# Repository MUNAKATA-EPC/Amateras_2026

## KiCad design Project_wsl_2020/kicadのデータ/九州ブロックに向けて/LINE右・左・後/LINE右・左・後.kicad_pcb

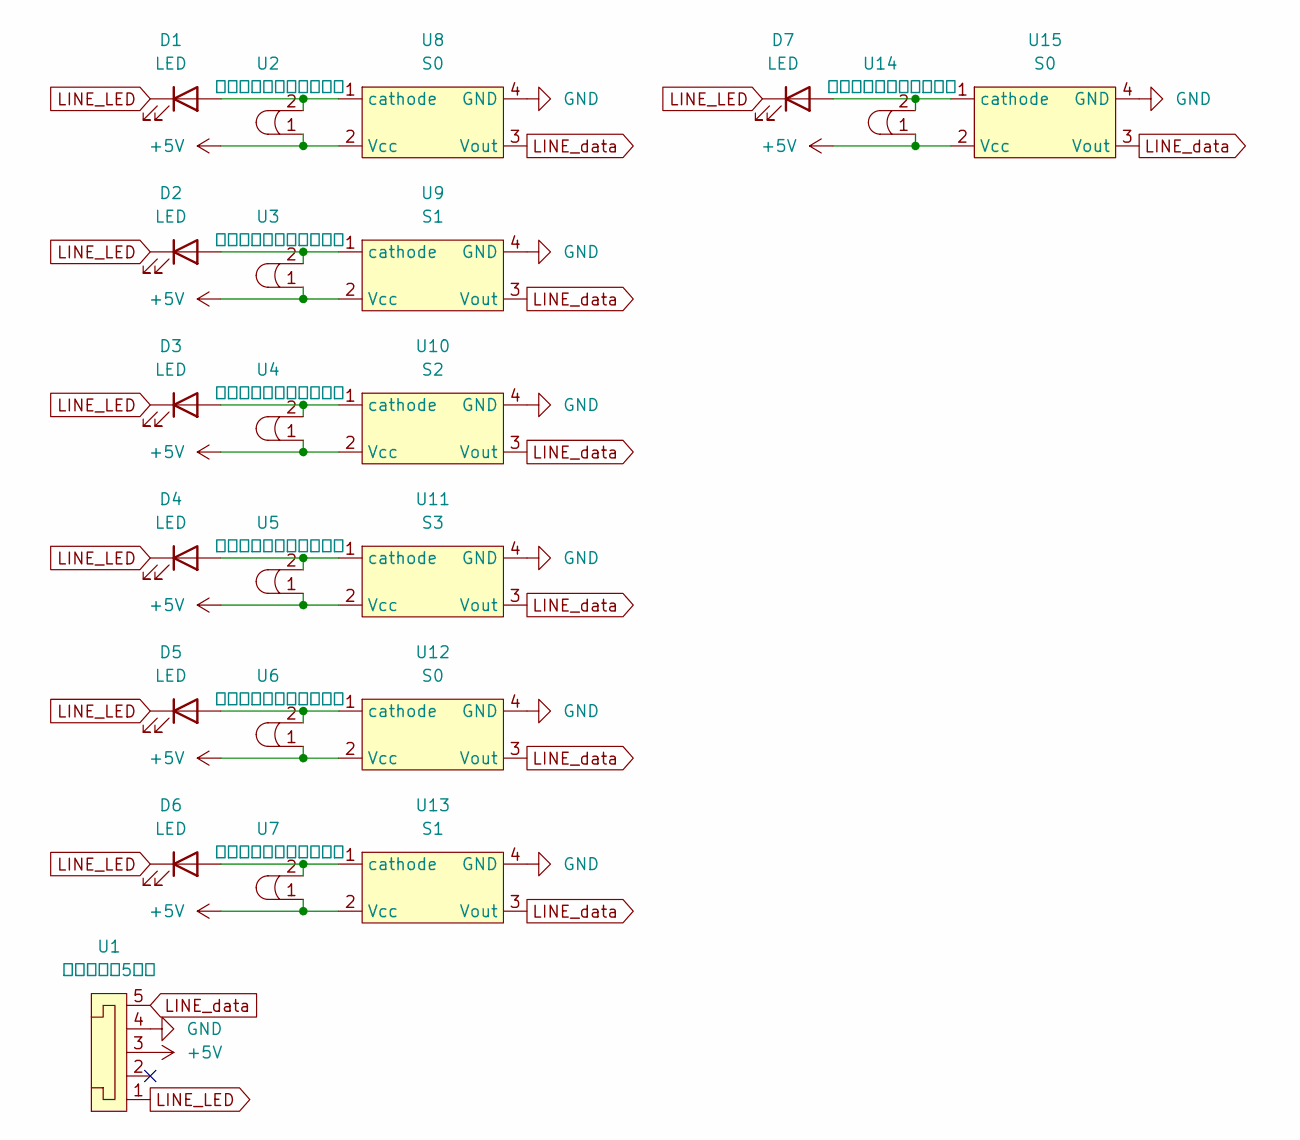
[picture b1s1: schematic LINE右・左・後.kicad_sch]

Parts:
D1, D2, D3, D4, D5, D6, D7: LED
U1: コネクター5ピン; L字コネクター5ピン
U2, U3, U4, U5, U6, U7, U14: セラミックコンデンサー
U8, U12, U15: S0; S4282-51,S7136
U9, U13: S1; S4282-51,S7136
U10: S2; S4282-51,S7136
U11: S3; S4282-51,S7136

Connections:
+5V: U1.3, U2.1, U3.1, U4.1, U5.1, U6.1, U7.1, U8.2 (Vcc), U9.2 (Vcc), U10.2 (Vcc), U11.2 (Vcc), U12.2 (Vcc), U13.2 (Vcc), U14.1, U15.2 (Vcc)
GND: U1.4, U8.4 (GND), U9.4 (GND), U10.4 (GND), U11.4 (GND), U12.4 (GND), U13.4 (GND), U15.4 (GND)
LINE_LED: D1.1 (K), D2.1 (K), D3.1 (K), D4.1 (K), D5.1 (K), D6.1 (K), D7.1 (K), U1.1
LINE_data: U1.5, U8.3 (Vout), U9.3 (Vout), U10.3 (Vout), U11.3 (Vout), U12.3 (Vout), U13.3 (Vout), U15.3 (Vout)
unnamed: D1.2 (A), U2.2, U8.1 (cathode)
unnamed: D2.2 (A), U3.2, U9.1 (cathode)
unnamed: D3.2 (A), U4.2, U10.1 (cathode)
unnamed: D4.2 (A), U5.2, U11.1 (cathode)
unnamed: D5.2 (A), U6.2, U12.1 (cathode)
unnamed: D6.2 (A), U7.2, U13.1 (cathode)
unnamed: D7.2 (A), U14.2, U15.1 (cathode)

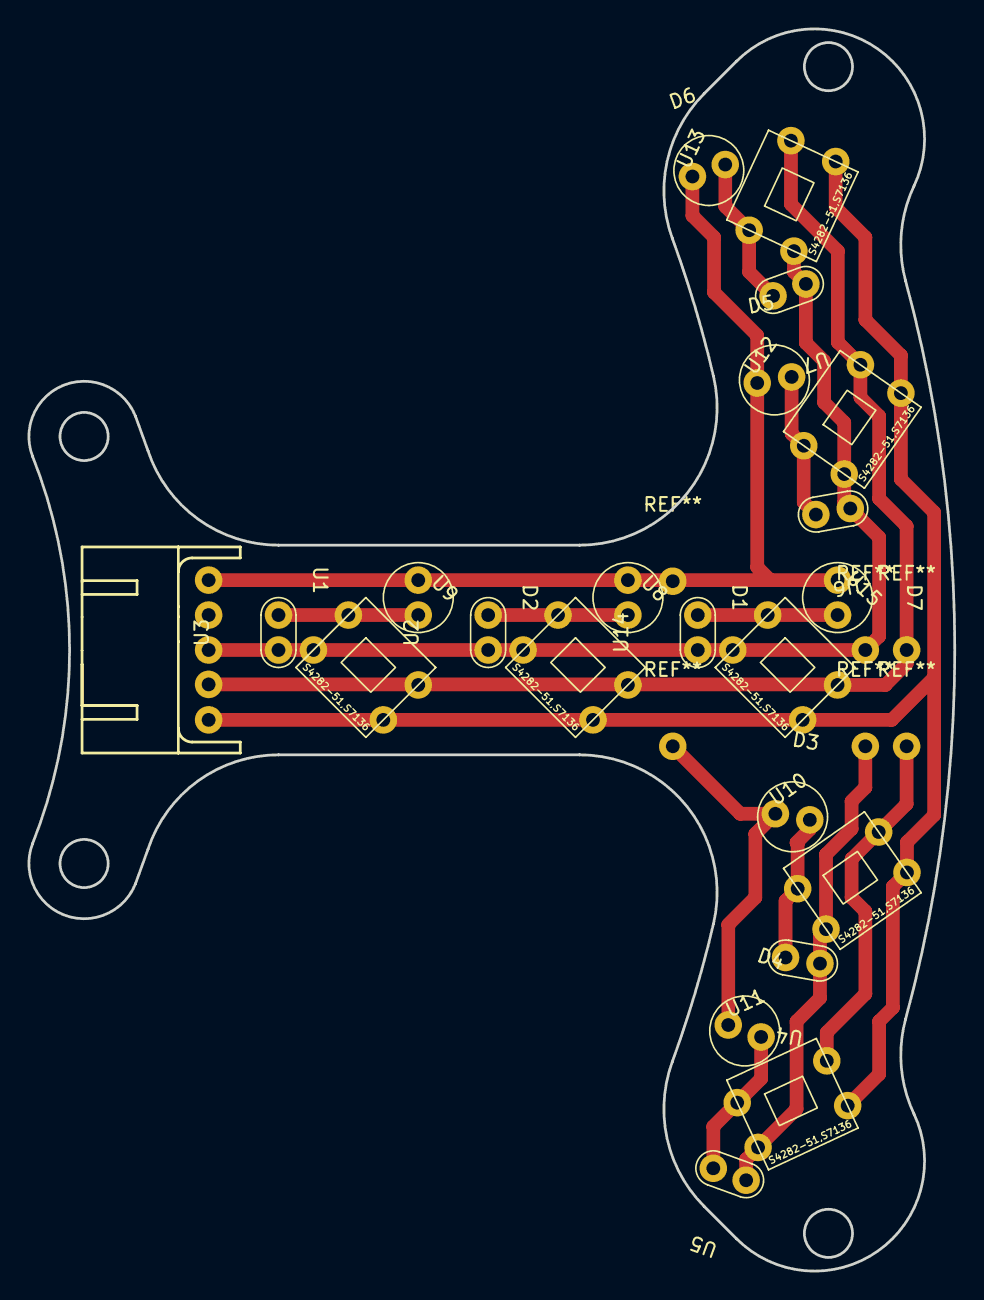
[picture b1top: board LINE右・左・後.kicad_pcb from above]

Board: 2 copper layers, 67.3 x 90.3 mm, 22 parts (0 on the bottom side), 11 nets.

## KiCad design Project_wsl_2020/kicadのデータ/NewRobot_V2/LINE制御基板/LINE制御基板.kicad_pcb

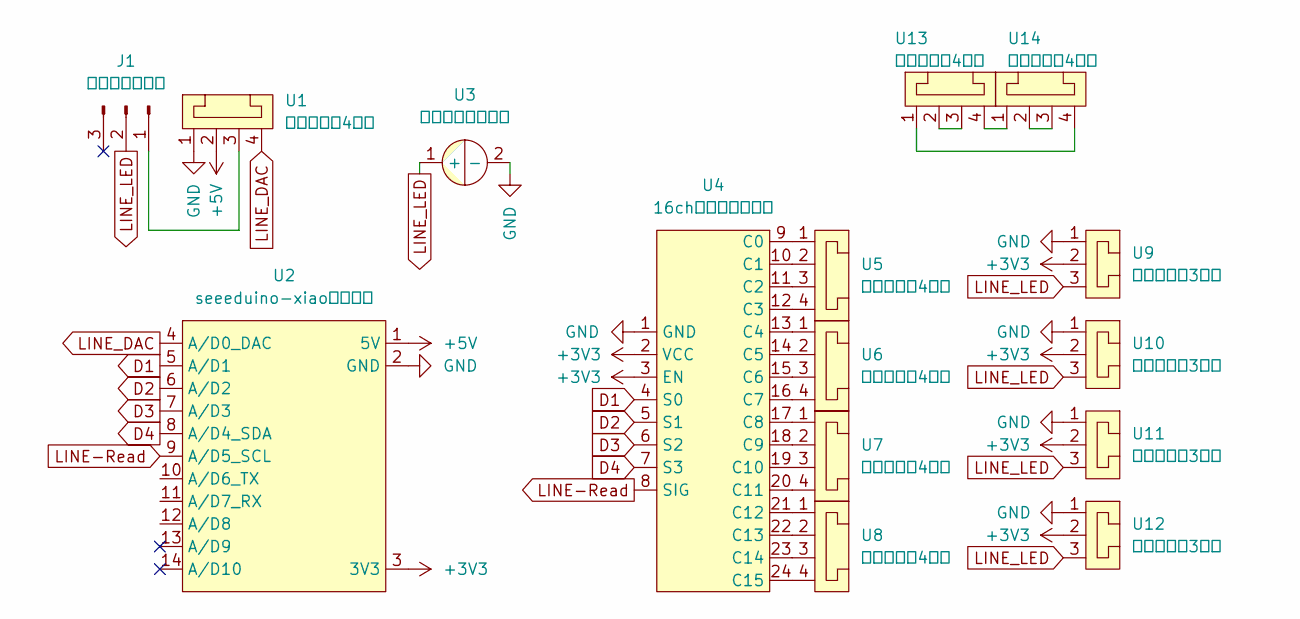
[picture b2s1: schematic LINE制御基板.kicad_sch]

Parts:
J1: トグルスイッチ; 基板用トグルスイッチ
U1, U5, U6, U7, U8, U13, U14: コネクター4ピン
U2: seeeduino-xiaoマイコン
U3: 電解コンデンサー
U4: 16chマルチプレクサ; マルチプレクサ
U9, U10, U11, U12: コネクター3ピン

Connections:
+3V3: U2.3 (3V3), U4.2 (VCC), U9.2, U10.2, U11.2, U12.2
+5V: U1.2, U2.1 (5V)
D1: U2.5 (A/D1), U4.4 (S0)
D2: U2.6 (A/D2), U4.5 (S1)
D3: U2.7 (A/D3), U4.6 (S2)
D4: U2.8 (A/D4_SDA), U4.7 (S3)
GND: U1.1, U2.2 (GND), U3.2 (-), U4.1 (GND), U9.1, U10.1, U11.1, U12.1
LINE_DAC: U1.4, U2.4 (A/D0_DAC)
LINE_LED: J1.2, U3.1 (+), U9.3, U10.3, U11.3, U12.3
unnamed: J1.1, U1.3
unnamed: U4.9 (C0), U5.1
unnamed: U4.10 (C1), U5.2
unnamed: U4.11 (C2), U5.3
unnamed: U4.12 (C3), U5.4
unnamed: U4.13 (C4), U6.1
unnamed: U4.14 (C5), U6.2
unnamed: U4.15 (C6), U6.3
unnamed: U4.16 (C7), U6.4
unnamed: U4.17 (C8), U7.1
unnamed: U4.18 (C9), U7.2
unnamed: U4.19 (C10), U7.3
unnamed: U4.20 (C11), U7.4
unnamed: U4.21 (C12), U8.1
unnamed: U4.22 (C13), U8.2
unnamed: U4.23 (C14), U8.3
unnamed: U4.24 (C15), U8.4
unnamed: U13.1, U14.4
unnamed: U13.2, U13.3
unnamed: U13.4, U14.1
unnamed: U14.2, U14.3

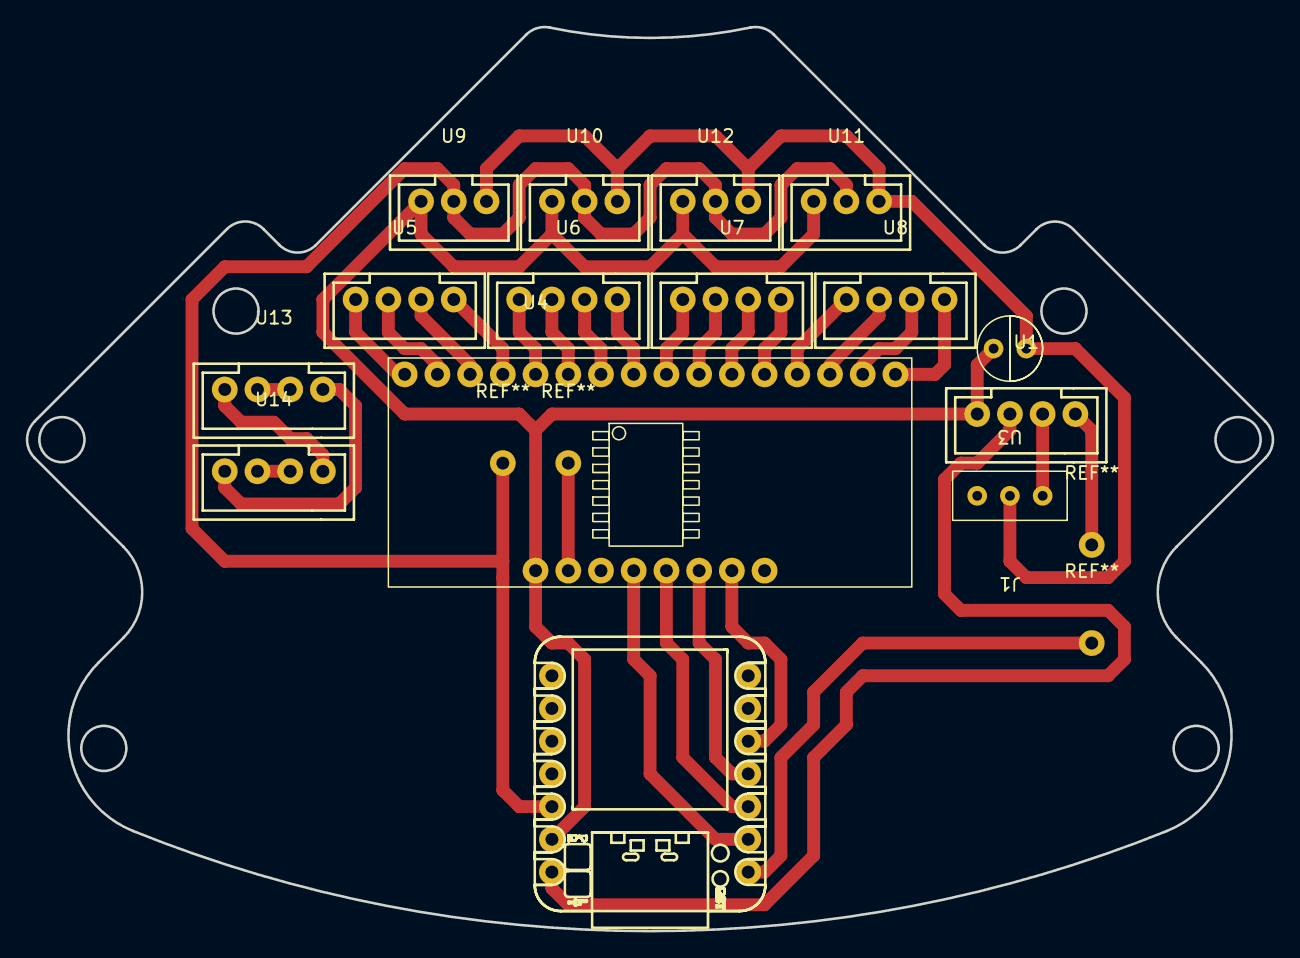
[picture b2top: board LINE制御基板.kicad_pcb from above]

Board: 2 copper layers, 96.7 x 70.2 mm, 15 parts (0 on the bottom side), 30 nets.

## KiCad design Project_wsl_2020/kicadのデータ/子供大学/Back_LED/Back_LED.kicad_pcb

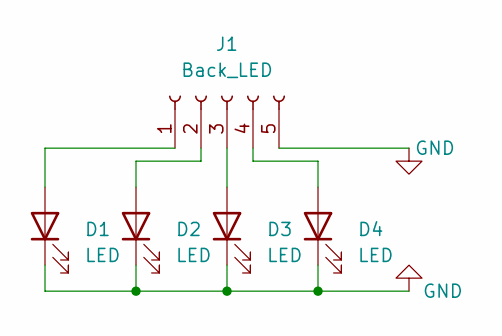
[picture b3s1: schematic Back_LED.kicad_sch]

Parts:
D1, D2, D3, D4: LED; PinSocket_1x02_P2.54mm_Horizontal
J1: Back_LED; PinSocket_1x05_P2.54mm_Vertical

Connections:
GND: D1.1 (K), D2.1 (K), D3.1 (K), D4.1 (K), J1.5
unnamed: D1.2 (A), J1.1
unnamed: D2.2 (A), J1.2
unnamed: D3.2 (A), J1.3
unnamed: D4.2 (A), J1.4

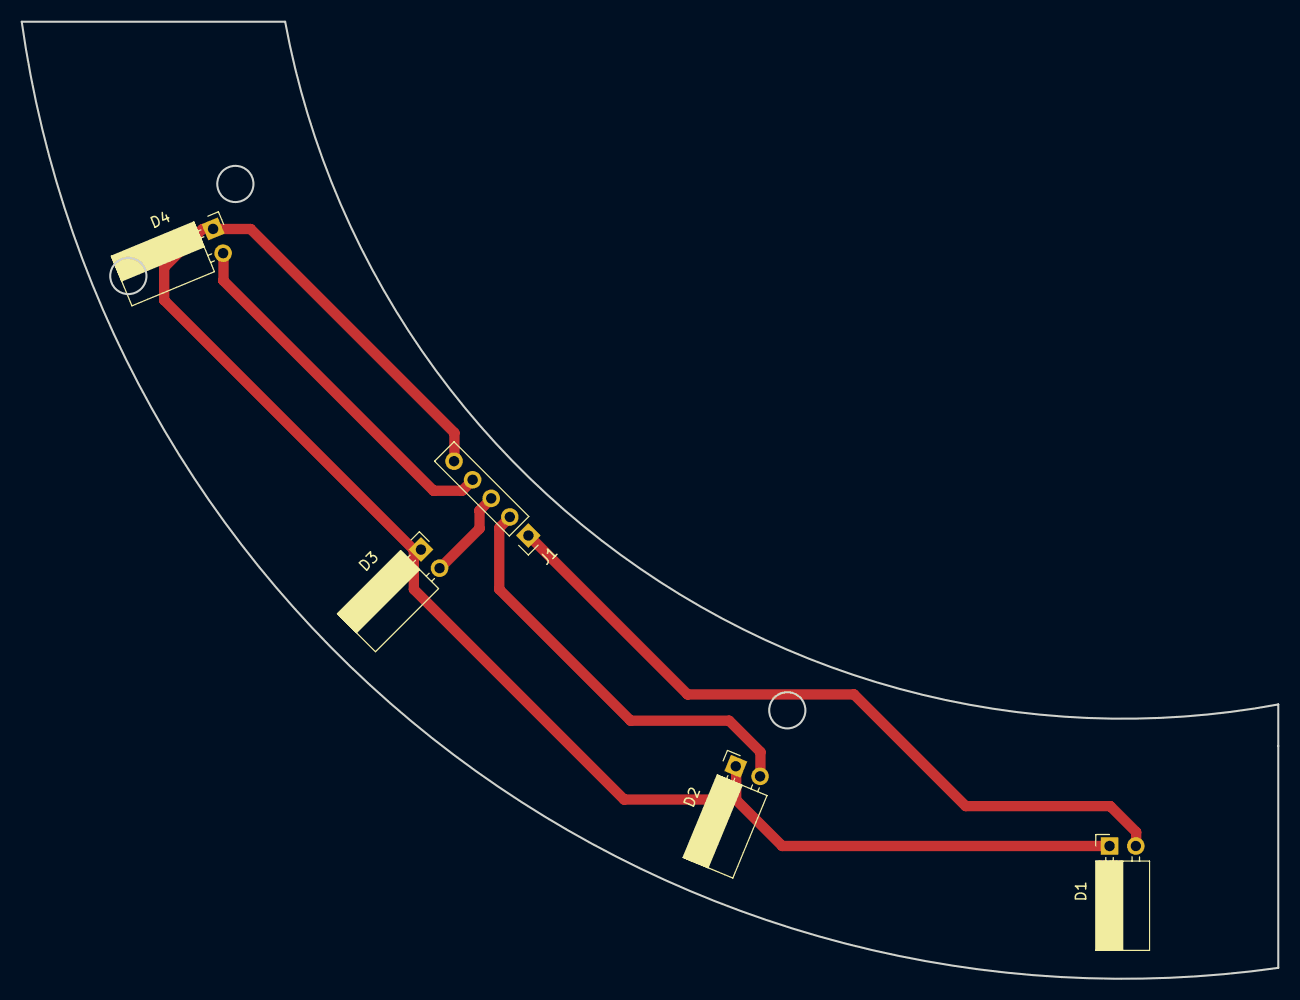
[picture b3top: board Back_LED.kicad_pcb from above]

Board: 2 copper layers, 121.4 x 92.5 mm, 5 parts (0 on the bottom side), 5 nets.

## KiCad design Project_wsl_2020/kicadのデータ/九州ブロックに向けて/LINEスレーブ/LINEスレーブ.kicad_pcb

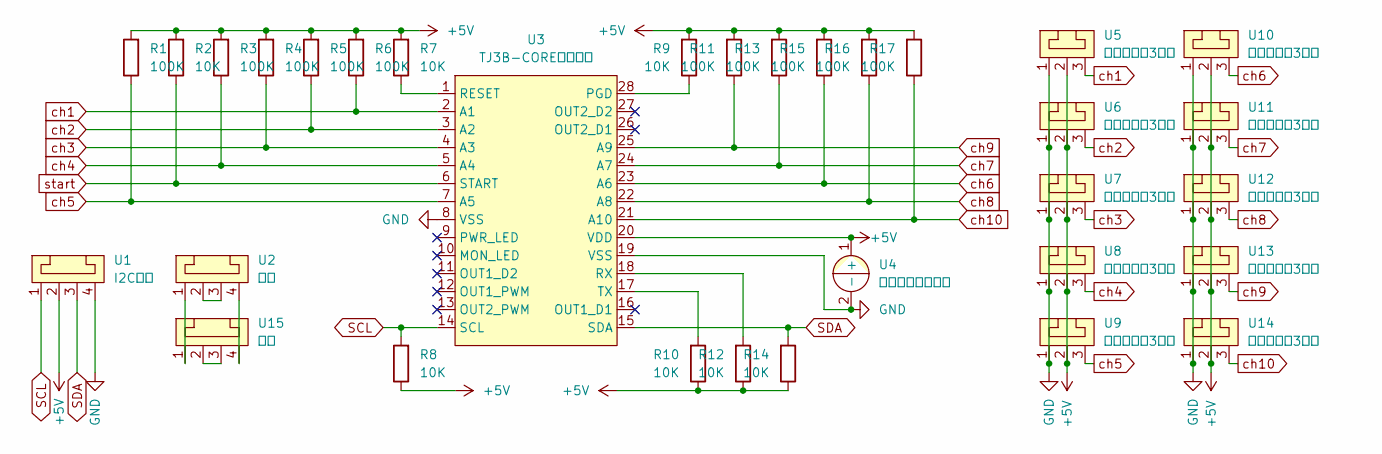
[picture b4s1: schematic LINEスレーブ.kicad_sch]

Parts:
R1, R3, R4, R5, R6, R11, R13, R15, R16, R17: 100K; 抵抗
R2, R7, R8, R9, R10, R12, R14: 10K; 抵抗
U1: I2Cピン; コネクター4ピン
U2, U15: 電池; コネクター4ピン
U3: TJ3B-COREマイコン
U4: 電解コンデンサー
U5, U6, U7, U8, U9, U10, U11, U12, U13, U14: コネクター3ピン

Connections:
+5V: R1.2, R2.2, R3.2, R4.2, R5.2, R6.2, R7.2, R8.1, R9.2, R10.1, R11.2, R12.1, R13.2, R14.1, R15.2, R16.2, R17.2, U1.2, U3.20 (VDD), U4.1 (+), U5.2, U6.2, U7.2, U8.2, U9.2, U10.2, U11.2, U12.2, U13.2, U14.2
GND: U1.4, U3.8 (VSS), U3.19 (VSS), U4.2 (-), U5.1, U6.1, U7.1, U8.1, U9.1, U10.1, U11.1, U12.1, U13.1, U14.1
unnamed: R7.1, U3.1 (RESET)
unnamed: R9.1, U3.28 (PGD)
unnamed: R10.2, U3.17 (TX)
unnamed: R12.2, U3.18 (RX)
unnamed: U2.2, U2.3
unnamed: U2.1, U15.1
unnamed: U15.2, U15.3
unnamed: U2.4, U15.4
SCL: R8.2, U1.1, U3.14 (SCL)
SDA: R14.2, U1.3, U3.15 (SDA)
ch1: R6.1, U3.2 (A1), U5.3
ch2: R5.1, U3.3 (A2), U6.3
ch3: R4.1, U3.4 (A3), U7.3
ch4: R3.1, U3.5 (A4), U8.3
ch5: R1.1, U3.7 (A5), U9.3
ch6: R15.1, U3.23 (A6), U10.3
ch7: R13.1, U3.24 (A7), U11.3
ch8: R16.1, U3.22 (A8), U12.3
ch9: R11.1, U3.25 (A9), U13.3
ch10: R17.1, U3.21 (A10), U14.3
start: R2.1, U3.6 (START)

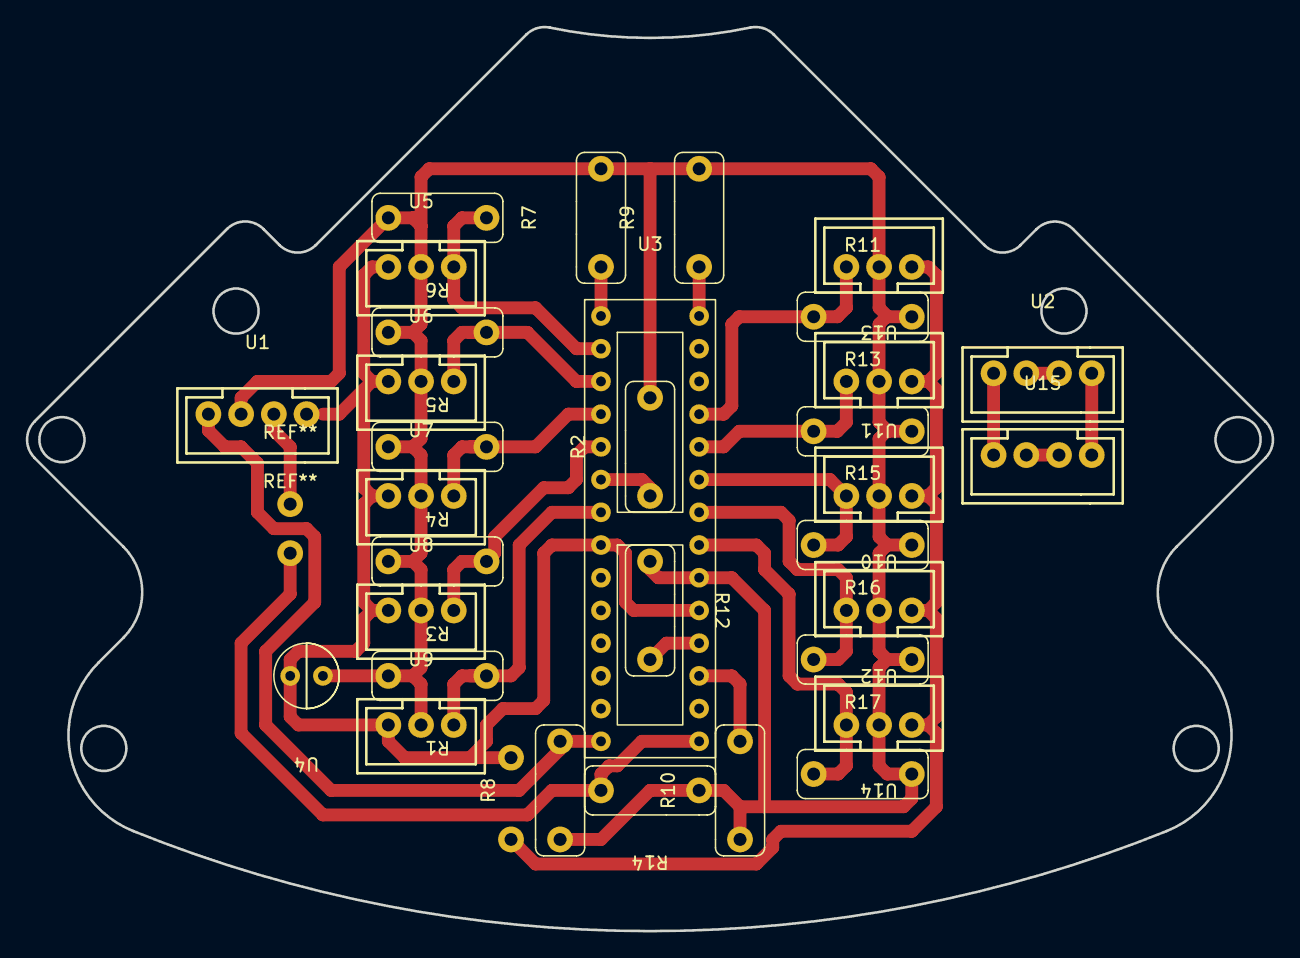
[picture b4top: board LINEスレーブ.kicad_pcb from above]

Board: 2 copper layers, 96.7 x 70.2 mm, 32 parts (0 on the bottom side), 23 nets.

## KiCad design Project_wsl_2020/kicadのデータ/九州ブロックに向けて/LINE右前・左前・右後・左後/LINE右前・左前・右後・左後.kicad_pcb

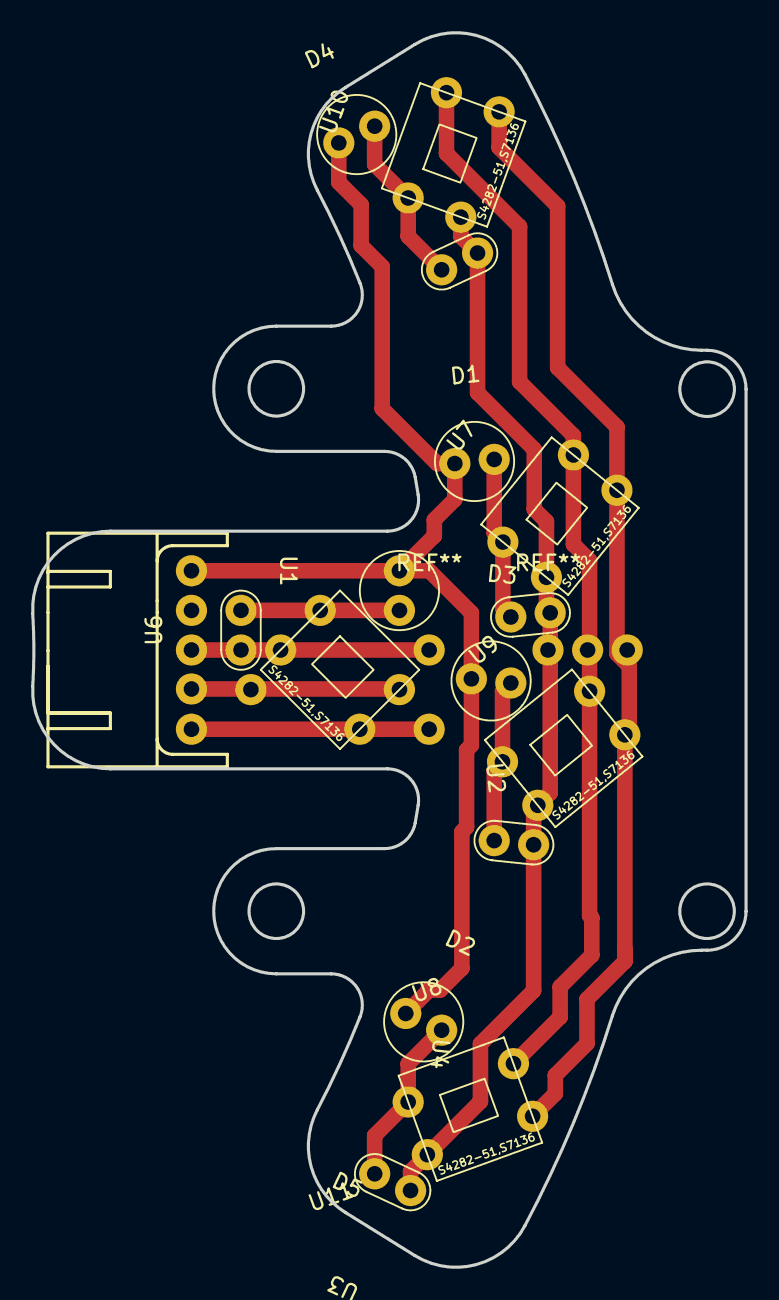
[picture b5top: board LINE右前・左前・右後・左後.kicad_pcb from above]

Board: 2 copper layers, 45.7 x 79.2 mm, 16 parts (0 on the bottom side), 9 nets.

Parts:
D1, D2, D3, D4, D5: LED
U1: コネクター5ピン; L字コネクター5ピン
U2, U3, U4, U5, U6: セラミックコンデンサー
U7, U11: S0; S4282-51,S7136
U8: S1; S4282-51,S7136
U9: S2; S4282-51,S7136
U10: S3; S4282-51,S7136

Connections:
+5V: U1.3, U2.1, U3.1, U4.1, U5.1, U6.1, U7.2 (Vcc), U8.2 (Vcc), U9.2 (Vcc), U10.2 (Vcc), U11.2 (Vcc)
GND: U1.4, U7.4 (GND), U8.4 (GND), U9.4 (GND), U10.4 (GND), U11.4 (GND)
LINE_LED: D1.1 (K), D2.1 (K), D3.1 (K), D4.1 (K), D5.1 (K), U1.1
LINE_data: U1.5, U7.3 (Vout), U8.3 (Vout), U9.3 (Vout), U10.3 (Vout), U11.3 (Vout)
unnamed: D1.2 (A), U2.2, U7.1 (cathode)
unnamed: D2.2 (A), U3.2, U8.1 (cathode)
unnamed: D3.2 (A), U4.2, U9.1 (cathode)
unnamed: D4.2 (A), U5.2, U10.1 (cathode)
unnamed: D5.2 (A), U6.2, U11.1 (cathode)

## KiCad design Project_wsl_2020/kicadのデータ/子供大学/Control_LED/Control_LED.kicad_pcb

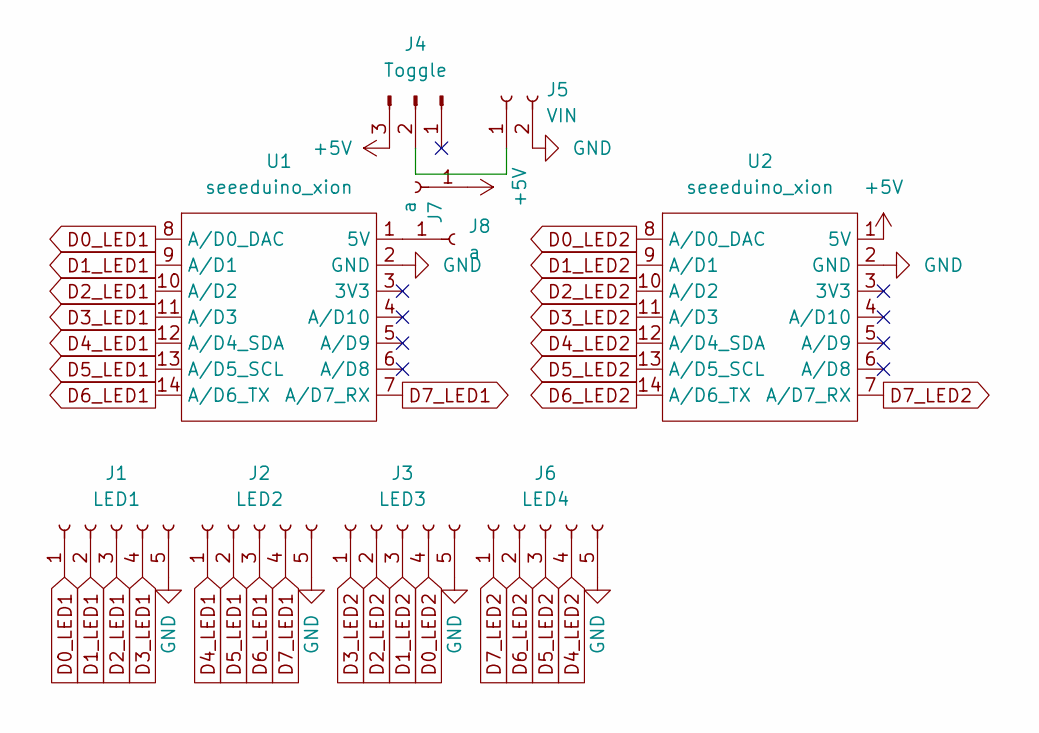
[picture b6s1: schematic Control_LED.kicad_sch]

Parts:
J1: LED1; PinSocket_1x05_P2.54mm_Vertical
J2: LED2; PinSocket_1x05_P2.54mm_Vertical
J3: LED3; PinSocket_1x05_P2.54mm_Vertical
J4: Toggle; PinSocket_1x03_P2.54mm_Vertical
J5: VIN; PinSocket_1x02_P2.54mm_Vertical
J6: LED4; PinSocket_1x05_P2.54mm_Vertical
J7, J8: a; PinSocket_1x01_P2.54mm_Vertical
U1, U2: seeeduino_xion; seeeduino_xiao

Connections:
+5V: J4.3, J7.1, U2.1 (5V)
D0_LED1: J1.1, U1.8 (A/D0_DAC)
D0_LED2: J3.4, U2.8 (A/D0_DAC)
D1_LED1: J1.2, U1.9 (A/D1)
D1_LED2: J3.3, U2.9 (A/D1)
D2_LED1: J1.3, U1.10 (A/D2)
D2_LED2: J3.2, U2.10 (A/D2)
D3_LED1: J1.4, U1.11 (A/D3)
D3_LED2: J3.1, U2.11 (A/D3)
D4_LED1: J2.1, U1.12 (A/D4_SDA)
D4_LED2: J6.4, U2.12 (A/D4_SDA)
D5_LED1: J2.2, U1.13 (A/D5_SCL)
D5_LED2: J6.3, U2.13 (A/D5_SCL)
D6_LED1: J2.3, U1.14 (A/D6_TX)
D6_LED2: J6.2, U2.14 (A/D6_TX)
D7_LED1: J2.4, U1.7 (A/D7_RX)
D7_LED2: J6.1, U2.7 (A/D7_RX)
GND: J1.5, J2.5, J3.5, J5.2, J6.5, U1.2 (GND), U2.2 (GND)
unnamed: J4.2, J5.1
unnamed: J8.1, U1.1 (5V)

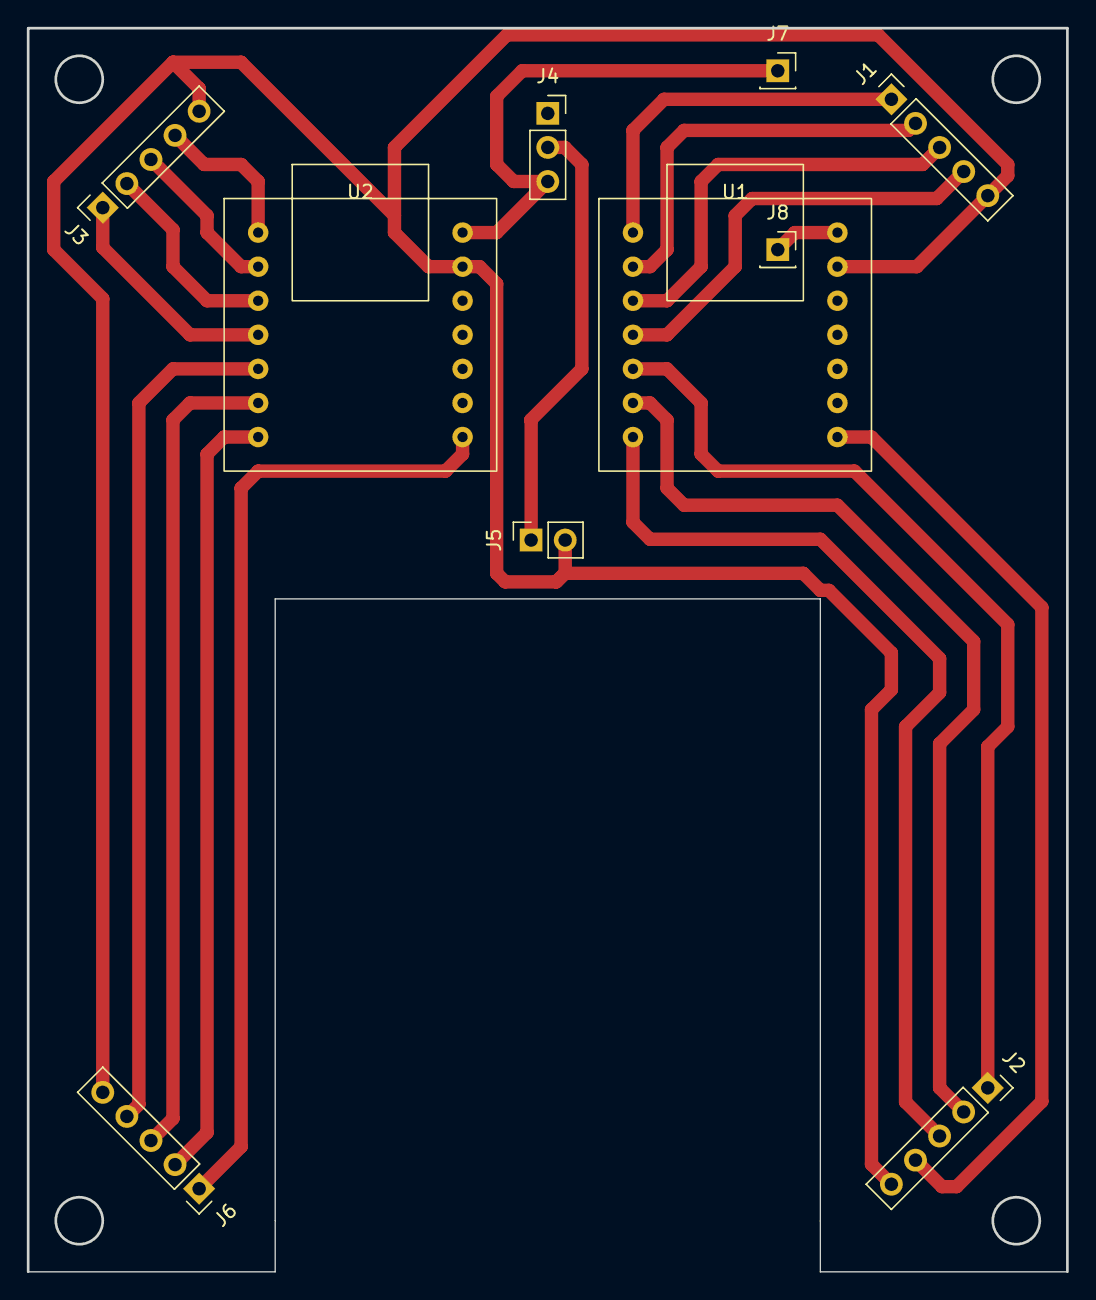
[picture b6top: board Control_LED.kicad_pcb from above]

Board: 2 copper layers, 77.5 x 92.7 mm, 10 parts (0 on the bottom side), 20 nets.

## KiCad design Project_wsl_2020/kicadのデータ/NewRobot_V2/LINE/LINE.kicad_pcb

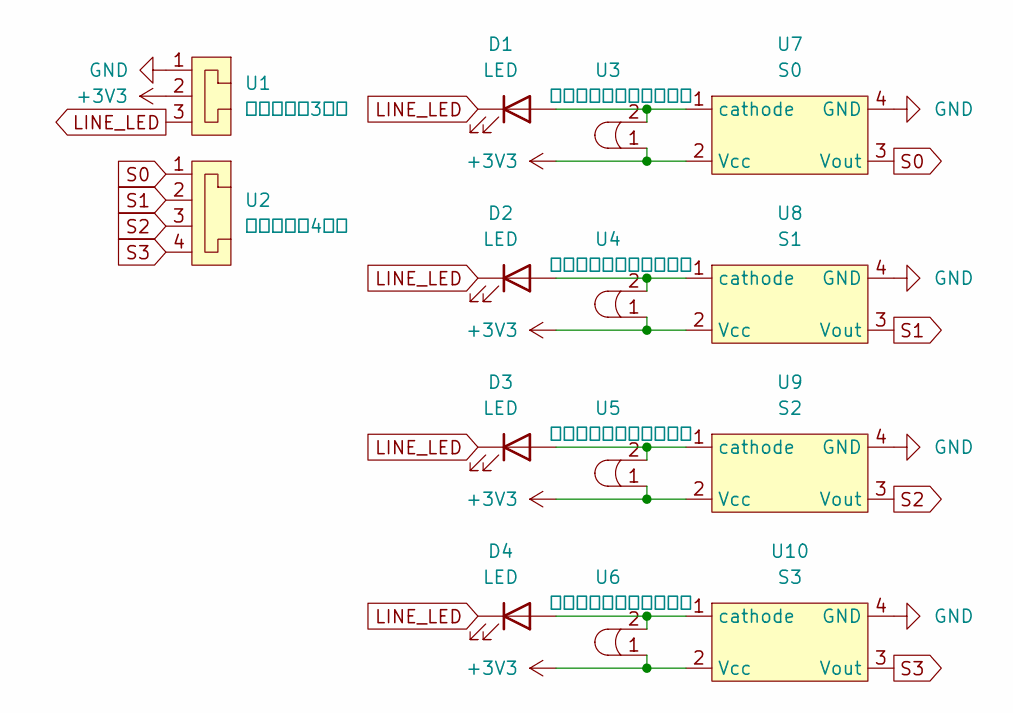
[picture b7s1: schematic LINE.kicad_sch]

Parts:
D1, D2, D3, D4: LED
U1: コネクター3ピン; L字コネクター3ピン
U2: コネクター4ピン; L字コネクター4ピン
U3, U4, U5, U6: セラミックコンデンサー
U7: S0; S4282-51,S7136
U8: S1; S4282-51,S7136
U9: S2; S4282-51,S7136
U10: S3; S4282-51,S7136

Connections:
+3V3: U1.2, U3.1, U4.1, U5.1, U6.1, U7.2 (Vcc), U8.2 (Vcc), U9.2 (Vcc), U10.2 (Vcc)
GND: U1.1, U7.4 (GND), U8.4 (GND), U9.4 (GND), U10.4 (GND)
LINE_LED: D1.1 (K), D2.1 (K), D3.1 (K), D4.1 (K), U1.3
unnamed: D1.2 (A), U3.2, U7.1 (cathode)
unnamed: D2.2 (A), U4.2, U8.1 (cathode)
unnamed: D3.2 (A), U5.2, U9.1 (cathode)
unnamed: D4.2 (A), U6.2, U10.1 (cathode)
S0: U2.1, U7.3 (Vout)
S1: U2.2, U8.3 (Vout)
S2: U2.3, U9.3 (Vout)
S3: U2.4, U10.3 (Vout)

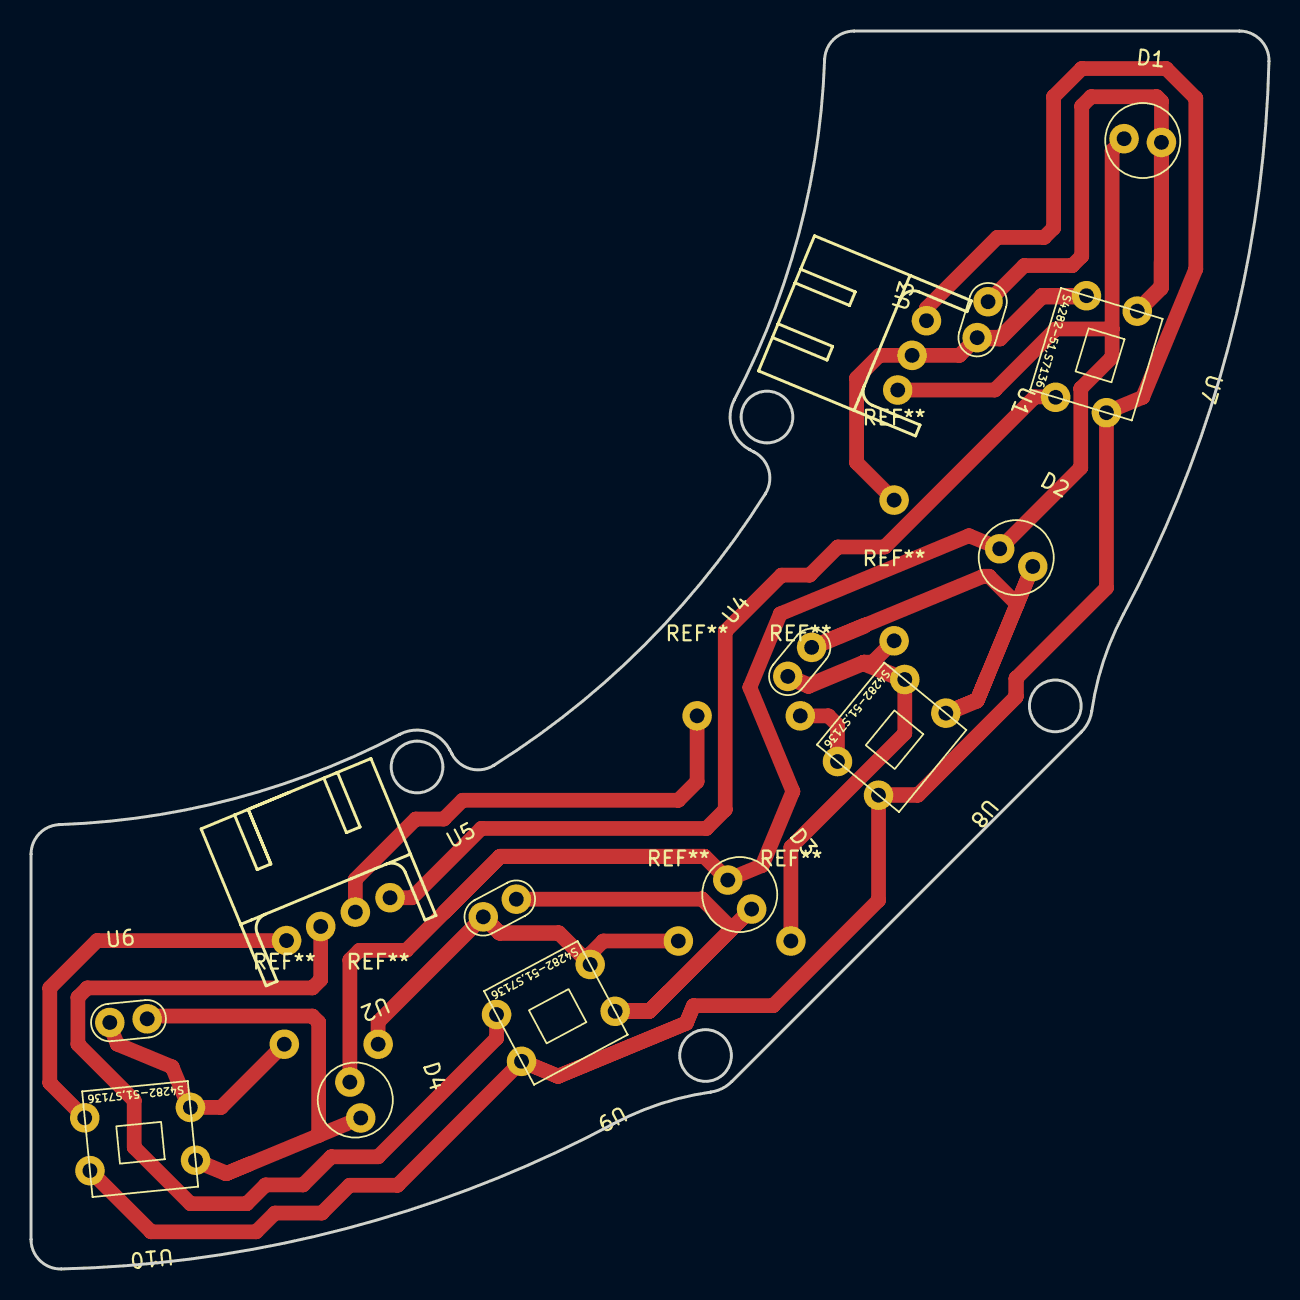
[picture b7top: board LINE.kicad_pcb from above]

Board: 2 copper layers, 83.8 x 83.8 mm, 14 parts (0 on the bottom side), 11 nets.

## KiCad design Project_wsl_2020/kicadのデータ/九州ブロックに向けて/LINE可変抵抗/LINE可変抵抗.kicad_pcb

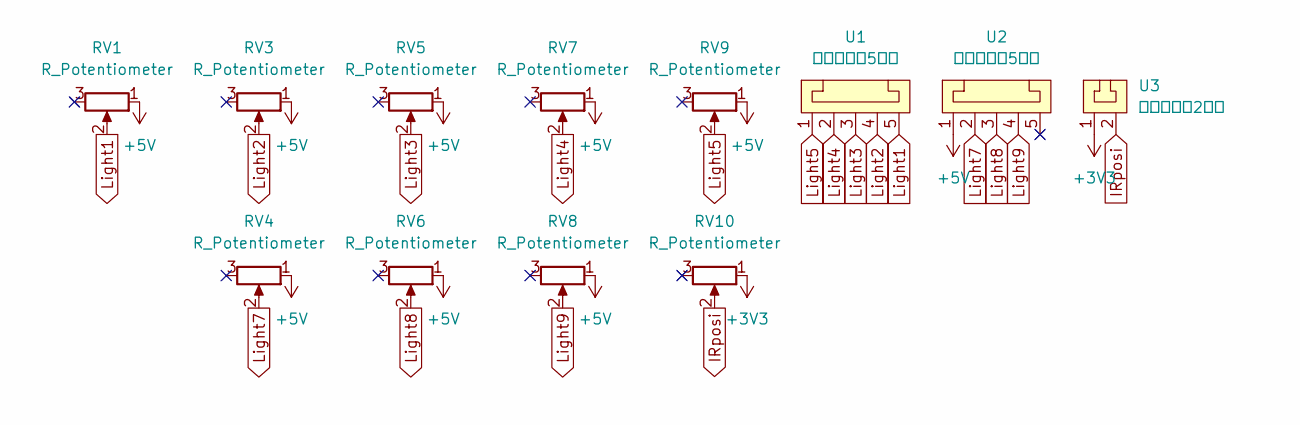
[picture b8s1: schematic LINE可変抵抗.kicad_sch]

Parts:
RV1, RV3, RV4, RV5, RV6, RV7, RV8, RV9, RV10: R_Potentiometer; Potentiometer
U1, U2: コネクター5ピン
U3: コネクター2ピン; L字コネクター2ピン

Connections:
+3V3: RV10.1, U3.1
+5V: RV1.1, RV3.1, RV4.1, RV5.1, RV6.1, RV7.1, RV8.1, RV9.1, U2.1
IRposi: RV10.2, U3.2
Light1: RV1.2, U1.5
Light2: RV3.2, U1.4
Light3: RV5.2, U1.3
Light4: RV7.2, U1.2
Light5: RV9.2, U1.1
Light7: RV4.2, U2.2
Light8: RV6.2, U2.3
Light9: RV8.2, U2.4

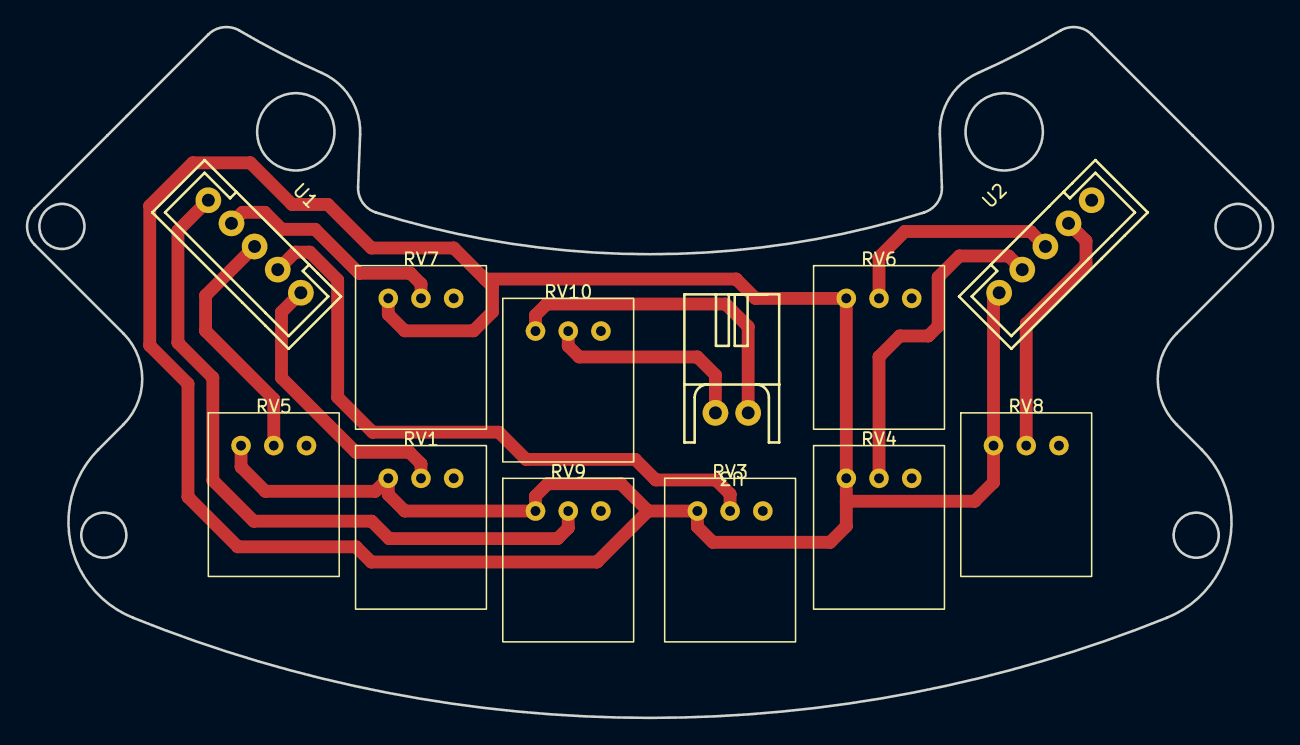
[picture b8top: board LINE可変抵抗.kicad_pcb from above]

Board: 2 copper layers, 96.7 x 53.6 mm, 12 parts (0 on the bottom side), 11 nets.

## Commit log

2025-07-31 Reorganize project: add Project_wsl_2026 under Munako-Amateras
2025-07-31 Reinitialize repository with Munako-Amateras as root
2025-07-31 Convert Project_wsl_2026 from submodule to normal folder
2025-07-31 Add new text files in Hardware subfolders
2025-07-31 Add new software folders line_seeeduinoxiao and ir_seeeduinoxiao
2025-07-31 Rename -jyugon-.txt to Jugon.txt
2025-07-31 Rename -onigiri-.txt to YakiOnigiri.txt
2025-08-01 Update files from Visual Studio changes
2025-08-01 Rename function to compute and update platformio.ini
2025-08-01 Update main_tennsy4.0: remove compute.cpp, modify headers and source, add new compute files and wire library
2025-08-02 Update my file from ?
2025-08-03 upload new file
2025-08-03 upload!
2025-08-03 change file
2025-08-03 upload motors.hpp
2025-08-03 main.cpp is changed
2025-08-03 tyotto kaeta
2025-08-03 timer is changed
2025-08-03 motor.hpp is changed
2025-08-03 test is changed
2025-08-03 openmv is created
2025-08-03 almost at the top
2025-08-03 almost at the top!
2025-08-03 Yeah
2025-08-03 kicker
2025-08-04 almost at the tpop
2025-08-04 get to the top
2025-08-04 tired
2025-08-05 changed
2025-08-05 becoming super robot
2025-08-05 homework
2025-08-07 thanks
2025-08-07 half out
2025-08-09 radicon
2025-08-09 camera update!
2025-08-09 hello,m5stamp
2025-08-09 hello,ps3
2025-08-12 ps3 update
2025-08-12 camera
2025-08-12 これ日本語でもできるのか
2025-08-12 super update
2025-08-12 hyper ventilation
2025-08-21 byte mask
2025-08-21 bit mask
2025-08-21 int float
2025-08-21 line changed
2025-08-21 line
2025-08-21 ps3 revolution
2025-08-21 line revolution
2025-08-22 ir revolution
2025-08-22 int revolution
2025-08-24 asobi
2025-08-24 mawarikomi
2025-08-24 cooldown
2025-08-24 serial revolution
2025-08-25 camera revolution
2025-08-25 motors revolution
2025-08-27 radicon revolution
2025-08-27 pdpower revolution
2025-08-28 attacker revolution
2025-08-30 vector revolution
2025-08-30 mux revolution
2025-08-30 hello world
2025-08-30 revolution
2025-08-31 removed
2025-08-31 apply file renames and updates
2025-08-31 fix folder name case: Button -> button, etc
2025-08-31 rename lib/IR -> lib/ir (case change)
2025-09-01 degital
2025-09-01 bitSensor
2025-09-01 normalize file names: capitalize first letter
2025-09-01 hello new files
2025-09-01 fuuuuuuuuuuuuu
2025-09-01 Vector.hpp
2025-09-01 Timer.hpp
2025-09-02 ball sensor
2025-09-02 catchsensor
2025-09-02 folder
2025-09-02 new file
2025-09-02 sensors
2025-09-02 sensor
2025-09-03 kick
2025-09-07 README
2025-09-07 length
2025-09-07 drivers
2025-09-07 motors
2025-09-07 attacker
2025-09-07 tyuukann
2025-09-07 figital
2025-09-11 show
2025-09-25 dribbler
2025-09-25 m5stamp
2025-09-25 コンストラクタ
2025-09-26 actions
2025-10-11 heloow
2025-10-11 hello
2025-10-15 debug
2025-10-16 hello ver3!
2025-10-16 2113
2025-10-16 efewvw
2025-10-16 f..k
2025-10-17 1312
2025-10-17 1244234
2025-10-22 awsa
2025-10-25 2141
2025-10-26 hello Arduino
2025-11-23 ロボット1は調整して！2はちょっとはましなはず
2025-11-26 3224
2025-11-26 motors driver
2025-11-29 music
2025-11-30 auto_robo
2025-12-01 auto robo
2025-12-04 movement_average
2025-12-04 movement_ave
2025-12-06 robo_auto
2025-12-06 auto line
2025-12-07 packet
2025-12-07 robo
2025-12-07 line adjust
2025-12-07 PacketManager
2025-12-08 commo
2025-12-08 toggle
2025-12-11 time is running!
2025-12-12 line auto
2025-12-12 timer
2025-12-13 power
2025-12-14 2423
2025-12-16 23905u
2025-12-16 defence
2025-12-19 egre
2025-12-20 vkinre
2025-12-21 kuyashii
2025-12-21 234523
2025-12-23 rapidly
2025-12-24 2r34
2025-12-25 legd20h
2025-12-25 brfsr
2025-12-25 214r34
2025-12-26 wvgef
2026-01-07 brrt
2026-01-13 renew
2026-01-18 jam system
2026-03-06 hello,world
2026-03-14 中村要は穴井笑佳のことがまだ好き
2026-03-15 中村要はまだ穴井笑佳のことが好き
2026-03-24 defender
2026-03-25 normal_ver
2026-04-08 hello stm32
2026-04-15 kitagwa
